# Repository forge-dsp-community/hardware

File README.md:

# Forge DSP Hardware

Hardware-Erweiterungen für Forge DSP 96ELN/96ELN-3/96LN und ETON CORE D8, entworfen mit KiCad 10.

| Ordner | Inhalt | Issue |
|---|---|---|
| [`ExtensionPCB/`](ExtensionPCB) | Aufsatzplatine an Position 1 über X-EXT_AUDIO: Modulsteckplatz als Platinenrandstecker Samtec MEC1-120-02-F-D-EM2 (38 Kontakte, Module als 1,6-mm-Steckkarte), U.FL für S/PDIF, liegende FFC-Buchse für X105 (SPI), Lötpad für 12 V vom Meanwell-Netzteil, über Ferrit und Elko gefiltert als VAUX an Kontakt 39/40 | [#1](https://github.com/forge-dsp-community/hardware/issues/1) |
| [`UsbAudioPCB/`](UsbAudioPCB) | Nachbau der USB-Audio/COM-Platine V4.0i des Originals: XMOS XU208 (USB-Audio, I²S/S/PDIF an X104), CP2102 (USB-COM), microSD, QSPI-Flash, Stecker X101/X104 zum Mainboard. Neu: Aussparung über X-PDI für einen Dupont-Stecker. Erzeugt aus `tools/` | [#3](https://github.com/forge-dsp-community/hardware/issues/3) |
| [`forge_es9018_iv_opa_v30/`](forge_es9018_iv_opa_v30) | KiCad-Rekonstruktion der I/V-Ausgangsplatine V3.0 (96ELN) des Originals aus den Eagle-Renderings: LME49740 (I/V-Wandler) und LME49720 (Differenzverstärker), steckt in J1–J4 der [AD/DA-Trägerplatine](forge_es9018_pcm4202_ad_v40). Netzliste, Platine mit Leiterbahnen, lesbarer Schaltplan | – |
| [`forge_es9018_pcm4202_ad_v40/`](forge_es9018_pcm4202_ad_v40) | KiCad-Rekonstruktion der AD/DA-Trägerplatine V4.0 (96ELN, CORE D8) aus Eagle- und Gerber-Bildern: 3× PCM4202 (ADC), ES9018 (8-Kanal-DAC), PCA9554. **Unfertiger Zwischenstand:** 6 offene Verbindungen, viele Werte unbekannt | – |

Geplante Einschubmodule: Bluetooth ([#2](https://github.com/forge-dsp-community/hardware/issues/2)),
CAN über MCP2515 ([firmware#73](https://github.com/forge-dsp-community/firmware/issues/73)).

**Stand:** Entwürfe, nicht gefertigt, nicht am Gerät geprüft. Die USB-Audio-Platine ist platziert und geroutet (KiCad-DRC ohne Fehler außer den bekannten Überlappungen von X102/X103/X105/SW101), noch ohne Impedanzprüfung beim Fertiger. Die Rekonstruktion des AD/DA-Trägers ist ein unpolierter Zwischenstand und nicht zum Fertigen gedacht.

## Ansichten

| | Seite F (KiCad vorne) | Seite B (KiCad hinten) |
|---|---|---|
| ExtensionPCB |  |  |
| UsbAudioPCB |  |  |
| I/V-Ausgang V3.0 |  |  |
| AD/DA-Träger V4.0 (unfertig) |  |  |

3D-Renderings aus KiCad (`kicad-cli pcb render`). Die USB-Audio-Platine sitzt im Forge mit **Seite B nach oben**:
Seite F zeigt zum Mainboard und trägt wie im Original nur microSD-Halter und USB-B-Buchse an der Kante, alle anderen
Bauteile sitzen auf B, die Stiftleisten X101/X104 stecken von B durch die Platine ins Mainboard. Bei der USB-Audio-Platine fehlen noch die Modelle von USB-B-Buchse,
microSD-Halter und Taster.

## USB-Audio-Platine erzeugen

Alles unter `UsbAudioPCB/tools/`, pcbnew-Python von KiCad 10 (`/usr/bin/python3`):

1. `gen_sch.py`, `gen_pcb.py`: Schaltplan und Platine aus `parts.py`/`placement.py`.
2. `fanout.py`: Durchkontaktierungen der Ebenennetze (GND auf In1, +3V3/XMOS.3V3/XMOS.1V0 auf In2).
3. `route_nc.py UsbAudioPCB.kicad_pcb 40 routed.kicad_pcb`: Raster-Router (0,1 mm, 45°) mit PathFinder-Verhandlung,
   gibt je Runde die Konfliktstellen aus und speichert den besten Stand (rund 70 min).
4. `cleanup.py routed.kicad_pcb`: Netze mit DRC-Fehlern neu routen (half beim aktuellen Stand nicht).
5. `fix_route.py`: Handkorrekturen für genau diesen Lauf, danach Zonen füllen und `kicad-cli pcb drc`.

`opt_place.py` sucht Drehungen und Tausche nach Ratsnest-Kreuzungen, `netmap.py` zeichnet Prüfbilder mit Netznamen.

## Anschlüsse der Grundplatine

Belegung von X-EXT_AUDIO, X105 und EXT-SPDIF sowie die Versorgung stehen in
[#1](https://github.com/forge-dsp-community/hardware/issues/1).

## 3D-Modelle

- `ExtensionPCB/Straddle.pretty/FH12-16S-0.5SH.stp` (liegend, eingebaut) und `FH12-16S-0.5SV.stp` (stehend, frühere
  Fassung): FFC-Buchsen von **Hirose Electric Co., Ltd.** (© Hirose, von [hirose.com](https://www.hirose.com/)).
- `ExtensionPCB/Straddle.pretty/MEC1-120-02-F-D-EM2-TR.stp`: Platinenrandstecker MEC1-120-02-F-D-EM2 von
  **Samtec, Inc.** (© Samtec, über [samtec.com](https://www.samtec.com/products/mec1)/TraceParts).

Für beide gelten die Nutzungsbedingungen der Hersteller, nicht die Lizenz dieses Repos. Die übrigen Modelle kommen aus
der KiCad-Bibliothek.

Der Footprint `Samtec_MEC1-120-02-F-D-EM2` ist nach der Samtec-Zeichnung „Recommended PCB layout
MEC1-1XX-XX-XX-D-EMX-XX“ (Rev. H) gezeichnet; die Zeichnung selbst liegt nicht im Repo.

## Lizenz der USB-Audio-Platine

`UsbAudioPCB/` ist ein Nachbau der Platine `pcbs/usb/com_audio/V40i` von **Mark Duprau** (Forge DSP) und steht wie das
Original unter [CC BY-NC-SA 4.0](https://creativecommons.org/licenses/by-nc-sa/4.0/). Abweichungen vom Original sind in
`UsbAudioPCB/tools/parts.py` und `placement.py` mit `PORT` markiert.

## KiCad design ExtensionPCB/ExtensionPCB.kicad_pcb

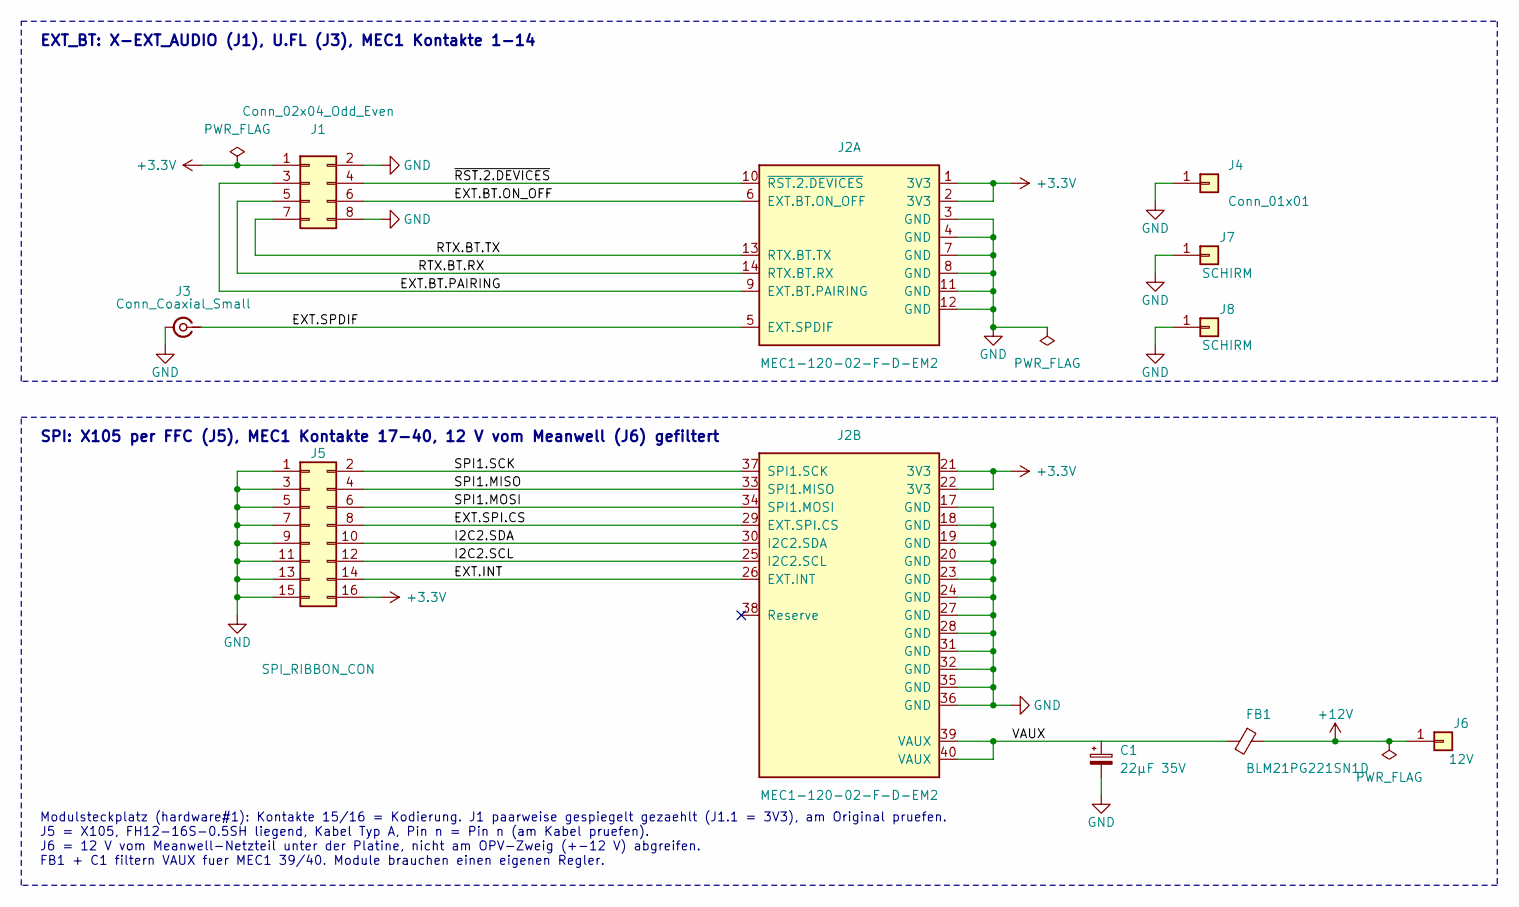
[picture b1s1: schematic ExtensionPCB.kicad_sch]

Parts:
C1: 22µF 35V; CP_Elec_5x5.4
FB1: BLM21PG221SN1D; L_0805_2012Metric
J1: Conn_02x04_Odd_Even; PinHeader_2x04_P2.54mm_Vertical
J2: MEC1-120-02-F-D-EM2; Samtec_MEC1-120-02-F-D-EM2
J3: Conn_Coaxial_Small; U.FL_Hirose_U.FL-R-SMT-1_Vertical
J4: Conn_01x01; SolderWire-1sqmm_1x01_D1.4mm_OD2.7mm
J5: SPI_RIBBON_CON; Hirose_FH12-16S-0.5SH_1x16-1MP_P0.50mm_Horizontal
J6: 12V; SolderWire-1sqmm_1x01_D1.4mm_OD2.7mm
J7: SCHIRM; ShieldTab_Chamfer_L
J8: SCHIRM; ShieldTab_Chamfer_R

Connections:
+3.3V: J1.1, J2.1 (3V3), J2.2 (3V3), J2.21 (3V3), J2.22 (3V3), J5.16
+12V: FB1.1, J6.1
/EXT.BT.ON_OFF: J1.6, J2.6 (EXT.BT.ON_OFF)
/EXT.BT.PAIRING: J1.3, J2.9 (EXT.BT.PAIRING)
/EXT.INT: J2.26 (EXT.INT), J5.14
/EXT.SPDIF: J2.5 (EXT.SPDIF), J3.1 (In)
/EXT.SPI.CS: J2.29 (EXT.SPI.CS), J5.8
/I2C2.SCL: J2.25 (I2C2.SCL), J5.12
/I2C2.SDA: J2.30 (I2C2.SDA), J5.10
/RTX.BT.RX: J1.5, J2.14 (RTX.BT.RX)
/RTX.BT.TX: J1.7, J2.13 (RTX.BT.TX)
/SPI1.MISO: J2.33 (SPI1.MISO), J5.4
/SPI1.MOSI: J2.34 (SPI1.MOSI), J5.6
/SPI1.SCK: J2.37 (SPI1.SCK), J5.2
/VAUX: C1.1, FB1.2, J2.39 (VAUX), J2.40 (VAUX)
/~RST.2.DEVICES: J1.4, J2.10 (~RST.2.DEVICES)
GND: C1.2, J1.2, J1.8, J2.3 (GND), J2.4 (GND), J2.7 (GND), J2.8 (GND), J2.11 (GND), J2.12 (GND), J2.17 (GND), J2.18 (GND), J2.19 (GND), J2.20 (GND), J2.23 (GND), J2.24 (GND), J2.27 (GND), J2.28 (GND), J2.31 (GND), J2.32 (GND), J2.35 (GND), J2.36 (GND), J3.2 (Ext), J4.1 (Pin_1_1), J5.1, J5.3, J5.5, J5.7, J5.9, J5.11, J5.13, J5.15, J7.1, J8.1

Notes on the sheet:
EXT_BT: X-EXT_AUDIO (J1), U.FL (J3), MEC1 Kontakte 1-14
SPI: X105 per FFC (J5), MEC1 Kontakte 17-40, 12 V vom Meanwell (J6) gefiltert
Modulsteckplatz (hardware#1): Kontakte 15/16 = Kodierung. J1 paarweise gespiegelt gezaehlt (J1.1 = 3V3), am Original pruefen. J5 = X105, FH12-16S-0.5SH liegend, Kabel Typ A, Pin n = Pin n (am Kabel pruefen). J6 = 12 V vom Meanwell-Netzteil unter der Platine, nicht am OPV-Zweig (+-12 V) abgreifen. F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

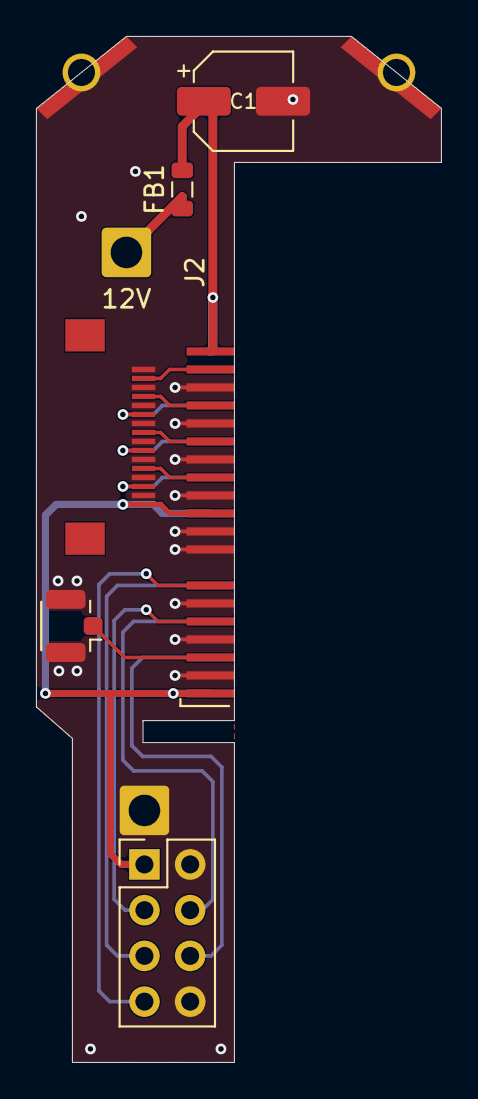
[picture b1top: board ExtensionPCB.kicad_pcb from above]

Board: 2 copper layers, 22.5 x 57.0 mm, 10 parts (0 on the bottom side), 17 nets.

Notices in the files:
UsbAudioPCB/UsbAudioPCB.kicad_sch:
Original: Mark Duprau, CC BY-NC-SA 4.0
